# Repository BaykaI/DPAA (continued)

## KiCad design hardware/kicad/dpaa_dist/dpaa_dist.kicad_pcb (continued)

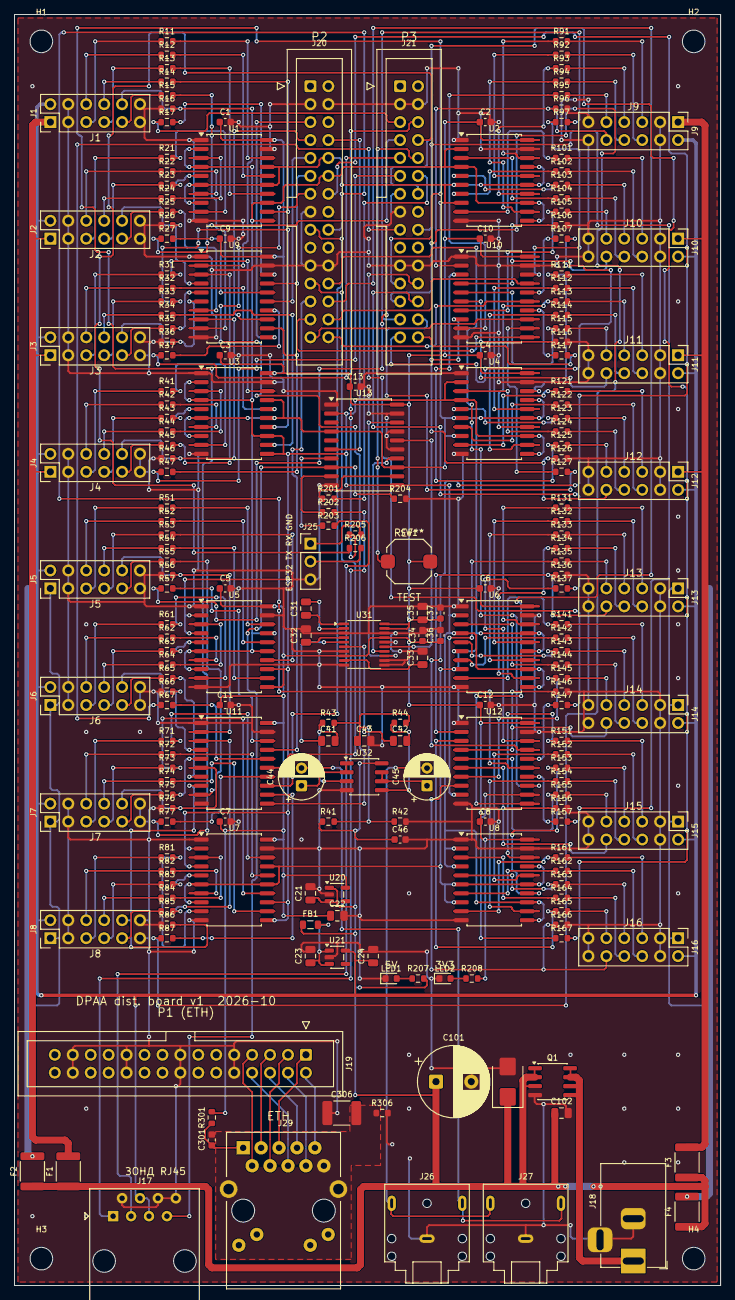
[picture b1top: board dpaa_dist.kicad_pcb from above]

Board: 2 copper layers, 100.0 x 180.0 mm, 216 parts (0 on the bottom side), 277 nets.

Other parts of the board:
H1, H2, H3, H4: M3; MountingHole_3.2mm_M3
R41#2, R42#2, R44#2: 33; R_0603_1608Metric
R43#2: 10k; R_0603_1608Metric

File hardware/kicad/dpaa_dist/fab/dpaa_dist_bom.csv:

Поз.;Кол-во;Значение;Корпус (KiCad);Наименование для заказа;LCSC (ориентир)
U1,U2,U3,U4,U5,U6,U7,U8,U9,U10,U11,U12,U13;13;74LVC244A;SOIC-20W_7.5x12.8mm_P1.27mm;SN74LVC244ADWR (TI) / 74LVC244AD (Nexperia);C7936
D1;1;SMBJ5.0A;D_SMB;SMBJ5.0A (Littelfuse/любой);C113978
R11,R12,R13,R14,R15,R17,R21,R22,R23,R24,R25,R27,R31,R32,R33,R34,R35,R37,R41,R42,R43,R44,R45,R47,R51,R52,R53,R54,R55,R57,R61,R62,R63,R64,R65,R67,R71,R72,R73,R74,R75,R77,R81,R82,R83,R84,R85,R87,R91,R92,R93,R94,R95,R97,R101,R102,R103,R104,R105,R107,R111,R112,R113,R114,R115,R117,R121,R122,R123,R124,R125,R127,R131,R132,R133,R134,R135,R137,R141,R142,R143,R144,R145,R147,R151,R152,R153,R154,R155,R157,R161,R162,R163,R164,R165,R167,R201,R202,R203;99;33;R_0603_1608Metric;резистор 0603 33 1%;
C35,C43,C102;3;10u;C_0805_2012Metric;конденсатор 0805 10u X7R/X5R 16 В;
LED1,LED2;2;LED;LED_0603_1608Metric;светодиод 0603 зелёный;C72043
C1,C2,C3,C4,C5,C6,C7,C8,C9,C10,C11,C12,C13,C34,C36,C37,C46,C301;18;100n;C_0603_1608Metric;конденсатор 0603 100n X7R 25 В;
J1,J2,J3,J4,J5,J6,J7,J8,J9,J10,J11,J12,J13,J14,J15,J16;16;2x6;PinHeader_2x06_P2.54mm_Vertical;штыревая гребёнка 2x6, 2,54 мм, прямая;C2337
R205,R206;2;100;R_0603_1608Metric;резистор 0603 100 1%;
R41,R42,R43,R44;4;10k;R_0603_1608Metric;резистор 0603 10k 1%;
R16,R26,R36,R46,R56,R66,R76,R86,R96,R106,R116,R126,R136,R146,R156,R166,R204;17;100k;R_0603_1608Metric;резистор 0603 100k 1%;
R207,R208;2;1k;R_0603_1608Metric;резистор 0603 1k 1%;
J19,J20,J21;3;IDC 2x15;IDC-Header_2x15_P2.54mm_Vertical;вилка IDC 2x15 (BH-30) с ключом, 2,54 мм;C2337
C44,C45;2;220u;CP_Radial_D6.3mm_P2.50mm;220 мкФ 6,3 В (10 В), Ø6,3 мм, шаг 2,5 мм;C2838
C21,C22,C23,C24,C41,C42;6;1u;C_0805_2012Metric;конденсатор 0805 1u X7R/X5R 16 В;
C101;1;1000u;CP_Radial_D10.0mm_P5.00mm;1000 мкФ 10 В, Ø10 мм, шаг 5 мм;C3326
J17;1;RJ45;RJ45_Amphenol_54602-x08_Horizontal;гнездо RJ45 8P8C без магнетиков (Amphenol 54602-908 или аналог);C86580
J26,J27;2;3.5mm;Jack_3.5mm_CUI_SJ1-3523N_Horizontal;гнездо 3,5 мм стерео, угловое (SJ1-3523N / PJ-320);C145816
J25;1;ESP32;PinHeader_1x03_P2.54mm_Vertical;штыревая гребёнка 1x3, 2,54 мм;C2337
SW1;1;кнопка;SW_Push_1TS009xxxx-xxxx-xxxx_6x6x5mm;кнопка тактовая 6x6x5 SMD;C318884
U20,U21;2;AP2112K-3.3;SOT-23-5;AP2112K-3.3TRG1 (Diodes);C51118
C31,C32,C33;3;2u2;C_0805_2012Metric;конденсатор 0805 2u2 X7R/X5R 16 В;
U32;1;TDA1308;SOIC-8_3.9x4.9mm_P1.27mm;TDA1308T/N2 (NXP);C77218
F1,F2,F3,F4;4;PTC 1.5A;Fuse_1812_4532Metric;PTC 1812 1,5 A 6 В (MF-MSMF150 или аналог);C70069
J18;1;5.5/2.1;BarrelJack_Horizontal;гнездо DC 5,5/2,1 мм (DC-005);C16214
U31;1;PCM5102A;TSSOP-20_4.4x6.5mm_P0.65mm;PCM5102APWR (TI);C107668
FB1;1;600R;L_0805_2012Metric;феррит 0805 600 Ом/100 МГц, 2 А;C1017
R306;1;1M;R_0603_1608Metric;резистор 0603 1 МОм 1%;
C306;1;1n 2kV;C_1812_4532Metric;конденсатор 1812 1 нФ 2 кВ X7R;C135917
Q1;1;AO4407A;SOIC-8_3.9x4.9mm_P1.27mm;AO4407A (Alpha & Omega);C77770
J29;1;RB1-125B8G1A;RJ45_UDE_RB1-125B8G1A;RJ45 MagJack 1000BASE-T UDE RB1-125B8G1A;C363353
